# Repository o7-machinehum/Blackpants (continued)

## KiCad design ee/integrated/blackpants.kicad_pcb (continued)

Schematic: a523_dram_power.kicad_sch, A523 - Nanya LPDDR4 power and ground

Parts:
C310: 10uF; C_0603_1608Metric; Voltage 10V
C311, C312, C313, C314, C315, C316, C317: 2.2uF; C_0402_1005Metric; Voltage 10V
C318: 100nF; C_0402_1005Metric; Voltage 10V
U301: NT6AN512T32AV-J2; FBGA-200_10x15mm_P0.8x0.65mm

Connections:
GND: C310.2, C311.2, C312.2, C313.2, C314.2, C315.2, C316.2, C317.2, C318.2, U301.A3 (VSS), U301.A10 (VSS), U301.AB3 (VSS), U301.AB5 (VSS), U301.AB8 (VSS), U301.AB10 (VSS), U301.C1 (VSS), U301.C5 (VSS), U301.C8 (VSS), U301.C12 (VSS), U301.D2 (VSS), U301.D4 (VSS), U301.D9 (VSS), U301.D11 (VSS), U301.E1 (VSS), U301.E5 (VSS), U301.E8 (VSS), U301.E12 (VSS), U301.G1 (VSS), U301.G3 (VSS), U301.G5 (VSS), U301.G8 (VSS), U301.G10 (VSS), U301.G12 (VSS), U301.J1 (VSS), U301.J3 (VSS), U301.J10 (VSS), U301.J12 (VSS), U301.K2 (VSS), U301.K4 (VSS), U301.K9 (VSS), U301.K11 (VSS), U301.N2 (VSS), U301.N4 (VSS), U301.N9 (VSS), U301.N11 (VSS), U301.P1 (VSS), U301.P3 (VSS), U301.P10 (VSS), U301.P12 (VSS), U301.T1 (VSS), U301.T3 (VSS), U301.T5 (VSS), U301.T8 (VSS), U301.T10 (VSS), U301.T12 (VSS), U301.V1 (VSS), U301.V5 (VSS), U301.V8 (VSS), U301.V12 (VSS), U301.W2 (VSS), U301.W4 (VSS), U301.W9 (VSS), U301.W11 (VSS), U301.Y1 (VSS), U301.Y5 (VSS), U301.Y8 (VSS), U301.Y12 (VSS); also elsewhere on the board
VCC_DRAM: C310.1, C311.1, C312.1, C313.1, C314.1, C315.1, C316.1, U301.A4 (VDD2), U301.A9 (VDD2), U301.AA3 (VDDQ), U301.AA5 (VDDQ), U301.AA8 (VDDQ), U301.AA10 (VDDQ), U301.AB4 (VDD2), U301.AB9 (VDD2), U301.B3 (VDDQ), U301.B5 (VDDQ), U301.B8 (VDDQ), U301.B10 (VDDQ), U301.D1 (VDDQ), U301.D5 (VDDQ), U301.D8 (VDDQ), U301.D12 (VDDQ), U301.F3 (VDDQ), U301.F5 (VDD2), U301.F8 (VDD2), U301.F10 (VDDQ), U301.H1 (VDD2), U301.H5 (VDD2), U301.H8 (VDD2), U301.H12 (VDD2), U301.K1 (VDD2), U301.K3 (VDD2), U301.K10 (VDD2), U301.K12 (VDD2), U301.N1 (VDD2), U301.N3 (VDD2), U301.N10 (VDD2), U301.N12 (VDD2), U301.R1 (VDD2), U301.R5 (VDD2), U301.R8 (VDD2), U301.R12 (VDD2), U301.U3 (VDDQ), U301.U5 (VDD2), U301.U8 (VDD2), U301.U10 (VDDQ), U301.W1 (VDDQ), U301.W5 (VDDQ), U301.W8 (VDDQ), U301.W12 (VDDQ); also elsewhere on the board
VDD18_LPDDR: C317.1, C318.1, U301.F1 (VDD1), U301.F12 (VDD1), U301.G4 (VDD1), U301.G9 (VDD1), U301.T4 (VDD1), U301.T9 (VDD1), U301.U1 (VDD1), U301.U12 (VDD1); also elsewhere on the board

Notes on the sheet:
VDD1 = 1.8V BLDO2. VDD2 = VDDQ = 1.1V DCDC3. DNU pads: no tracks or vias. Place the capacitors beside the DRAM package. Follow Allwinner DDR constraints and the selected stack-up.

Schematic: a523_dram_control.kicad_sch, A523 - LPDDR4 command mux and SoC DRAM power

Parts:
C301, C302, C303, C304, C305, C306, C307, C308: 2.2uF; C_0402_1005Metric; Voltage 10V
C309: 100nF; C_0402_1005Metric; Voltage 10V
NT301: DRAM sense; NetTie-2_SMD_Pad0.5mm
R301: 120 / 1%; R_0402_1005Metric
R302: 240 / 1%; R_0402_1005Metric
U201: A523; Allwinner_A523_FCCSP-522_15x15mm_P0.5mm
U301: NT6AN512T32AV-J2; FBGA-200_10x15mm_P0.8x0.65mm

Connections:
/2GB LPDDR4/Command / DRAM supply/DDR_CA0_0: U201.AE29 (SA2), U301.H2 (CA0_a)
/2GB LPDDR4/Command / DRAM supply/DDR_CA0_1: U201.AE28 (SA11), U301.J2 (CA1_a)
/2GB LPDDR4/Command / DRAM supply/DDR_CA0_2: U201.AC26 (SA1), U301.H9 (CA2_a)
/2GB LPDDR4/Command / DRAM supply/DDR_CA0_3: U201.AC25 (SA10), U301.H10 (CA3_a)
/2GB LPDDR4/Command / DRAM supply/DDR_CA0_4: U201.AE26 (SA17), U301.H11 (CA4_a)
/2GB LPDDR4/Command / DRAM supply/DDR_CA0_5: U201.AE27 (SA9), U301.J11 (CA5_a)
/2GB LPDDR4/Command / DRAM supply/DDR_CA1_0: U201.AE21 (SBA1), U301.R2 (CA0_b)
/2GB LPDDR4/Command / DRAM supply/DDR_CA1_1: U201.AD21 (SA4), U301.P2 (CA1_b)
/2GB LPDDR4/Command / DRAM supply/DDR_CA1_2: U201.AG21 (SA8), U301.R9 (CA2_b)
/2GB LPDDR4/Command / DRAM supply/DDR_CA1_3: U201.AF21 (SBA0), U301.R10 (CA3_b)
/2GB LPDDR4/Command / DRAM supply/DDR_CA1_4: U201.AE23 (SA16), U301.R11 (CA4_b)
/2GB LPDDR4/Command / DRAM supply/DDR_CA1_5: U201.AG25 (SACT), U301.P11 (CA5_b)
/2GB LPDDR4/Command / DRAM supply/DDR_CK0_N: U201.AJ26 (SCKN), U301.J9 (CK_N_a)
/2GB LPDDR4/Command / DRAM supply/DDR_CK0_P: U201.AH26 (SCKP), U301.J8 (CK_P_a)
/2GB LPDDR4/Command / DRAM supply/DDR_CK1_N: U201.AJ25 (SA15), U301.P9 (CK_N_b)
/2GB LPDDR4/Command / DRAM supply/DDR_CK1_P: U201.AH24 (SA14), U301.P8 (CK_P_b)
/2GB LPDDR4/Command / DRAM supply/DDR_CKE0: U201.AH27 (SCKE0), U301.J4 (CKE_a)
/2GB LPDDR4/Command / DRAM supply/DDR_CKE1: U201.AJ23 (SA6), U301.P4 (CKE_b)
/2GB LPDDR4/Command / DRAM supply/DDR_CS0: U201.AJ28 (SCS0), U301.H4 (CS_a)
/2GB LPDDR4/Command / DRAM supply/DDR_CS1: U201.AF25 (SA13), U301.R4 (CS_b)
/2GB LPDDR4/Command / DRAM supply/DDR_RESET_N: U201.AC19 (SRST), U301.T11 (RESET_N)
/2GB LPDDR4/Command / DRAM supply/DDR_ZQ: R302.2, U301.A5 (ZQ)
/2GB LPDDR4/Command / DRAM supply/SOC_DDR_ZQ: R301.1, U201.U25 (SZQ)
/VCC_DRAM_FB: NT301.2; also elsewhere on the board
GND: C301.2, C302.2, C303.2, C304.2, C305.2, C306.2, C307.2, C308.2, C309.2, R301.2; also elsewhere on the board
VCC_AVCC: C309.1, U201.AA21 (VDD18-DRAM); also elsewhere on the board
VCC_DRAM: C301.1, C302.1, C303.1, C304.1, C305.1, C306.1, C307.1, C308.1, NT301.1, R302.1, U201.T20 (VCC-DRAM), U201.T21 (VCC-DRAM), U201.T22 (VCC-DRAM), U201.U21 (VCC-DRAM), U201.V21 (VCC-DRAM), U201.W21 (VCC-DRAM), U201.Y14 (VCC-DRAML), U201.Y15 (VCC-DRAML), U201.Y16 (VCC-DRAML), U201.Y17 (VCC-DRAML), U201.Y19 (VCC-DRAML), U201.Y21 (VCC-DRAM), U301.G2 (ODT_CA_a), U301.T2 (ODT_CA_b); also elsewhere on the board

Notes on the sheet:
A523 LPDDR4 command mapping / load-side feedback
NT301: load-side sense to U501 FB3; allow >= 30mA. VCC_DRAM and VCC_DRAML both use 1.1V for LPDDR4. C301..C308 belong at the SoC DRAM ball clusters. Unused DDR3 command functions are unconnected.

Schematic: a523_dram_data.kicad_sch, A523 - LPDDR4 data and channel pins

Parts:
U201: A523; Allwinner_A523_FCCSP-522_15x15mm_P0.5mm
U301: NT6AN512T32AV-J2; FBGA-200_10x15mm_P0.8x0.65mm

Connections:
/2GB LPDDR4/Data channels/DDR_DM0: U201.AA29 (SDQM0), U301.C3 (DMI0_a)
/2GB LPDDR4/Data channels/DDR_DM1: U201.W28 (SDQM1), U301.C10 (DMI1_a)
/2GB LPDDR4/Data channels/DDR_DM2: U201.AH20 (SDQM2), U301.Y3 (DMI0_b)
/2GB LPDDR4/Data channels/DDR_DM3: U201.AJ16 (SDQM3), U301.Y10 (DMI1_b)
/2GB LPDDR4/Data channels/DDR_DQ0: U201.AA24 (SDQ0), U301.E4 (DQ5_a)
/2GB LPDDR4/Data channels/DDR_DQ1: U201.AA23 (SDQ1), U301.F4 (DQ4_a)
/2GB LPDDR4/Data channels/DDR_DQ2: U201.AC28 (SDQ2), U301.E2 (DQ2_a)
/2GB LPDDR4/Data channels/DDR_DQ3: U201.AD29 (SDQ3), U301.F2 (DQ3_a)
/2GB LPDDR4/Data channels/DDR_DQ4: U201.AA26 (SDQ4), U301.B2 (DQ0_a)
/2GB LPDDR4/Data channels/DDR_DQ5: U201.Y28 (SDQ5), U301.B4 (DQ7_a)
/2GB LPDDR4/Data channels/DDR_DQ6: U201.AA27 (SDQ6), U301.C2 (DQ1_a)
/2GB LPDDR4/Data channels/DDR_DQ7: U201.Y29 (SDQ7), U301.C4 (DQ6_a)
/2GB LPDDR4/Data channels/DDR_DQ8: U201.W23 (SDQ8), U301.E9 (DQ13_a)
/2GB LPDDR4/Data channels/DDR_DQ9: U201.W24 (SDQ9), U301.F9 (DQ12_a)
/2GB LPDDR4/Data channels/DDR_DQ10: U201.W26 (SDQ10), U301.B9 (DQ15_a)
/2GB LPDDR4/Data channels/DDR_DQ11: U201.W27 (SDQ11), U301.C9 (DQ14_a)
/2GB LPDDR4/Data channels/DDR_DQ12: U201.U29 (SDQ12), U301.C11 (DQ9_a)
/2GB LPDDR4/Data channels/DDR_DQ13: U201.U27 (SDQ13), U301.B11 (DQ8_a)
/2GB LPDDR4/Data channels/DDR_DQ14: U201.U24 (SDQ14), U301.F11 (DQ11_a)
/2GB LPDDR4/Data channels/DDR_DQ15: U201.U23 (SDQ15), U301.E11 (DQ10_a)
/2GB LPDDR4/Data channels/DDR_DQ16: U201.AH21 (SDQ16), U301.U2 (DQ3_b)
/2GB LPDDR4/Data channels/DDR_DQ17: U201.AJ21 (SDQ17), U301.V2 (DQ2_b)
/2GB LPDDR4/Data channels/DDR_DQ18: U201.AD19 (SDQ18), U301.U4 (DQ4_b)
/2GB LPDDR4/Data channels/DDR_DQ19: U201.AF19 (SDQ19), U301.Y2 (DQ1_b)
/2GB LPDDR4/Data channels/DDR_DQ20: U201.AG19 (SDQ20), U301.V4 (DQ5_b)
/2GB LPDDR4/Data channels/DDR_DQ21: U201.AH18 (SDQ21), U301.AA2 (DQ0_b)
/2GB LPDDR4/Data channels/DDR_DQ22: U201.AJ17 (SDQ22), U301.AA4 (DQ7_b)
/2GB LPDDR4/Data channels/DDR_DQ23: U201.AC17 (SDQ23), U301.Y4 (DQ6_b)
/2GB LPDDR4/Data channels/DDR_DQ24: U201.AC15 (SDQ24), U301.AA9 (DQ15_b)
/2GB LPDDR4/Data channels/DDR_DQ25: U201.AD15 (SDQ25), U301.AA11 (DQ8_b)
/2GB LPDDR4/Data channels/DDR_DQ26: U201.AF15 (SDQ26), U301.V11 (DQ10_b)
/2GB LPDDR4/Data channels/DDR_DQ27: U201.AG15 (SDQ27), U301.Y11 (DQ9_b)
/2GB LPDDR4/Data channels/DDR_DQ28: U201.AH17 (SDQ28), U301.U9 (DQ12_b)
/2GB LPDDR4/Data channels/DDR_DQ29: U201.AG17 (SDQ29), U301.U11 (DQ11_b)
/2GB LPDDR4/Data channels/DDR_DQ30: U201.AF17 (SDQ30), U301.Y9 (DQ14_b)
/2GB LPDDR4/Data channels/DDR_DQ31: U201.AD17 (SDQ31), U301.V9 (DQ13_b)
/2GB LPDDR4/Data channels/DDR_DQS0N: U201.AB29 (SDQS0N), U301.E3 (DQS_N0_a)
/2GB LPDDR4/Data channels/DDR_DQS0P: U201.AB28 (SDQS0P), U301.D3 (DQS_P0_a)
/2GB LPDDR4/Data channels/DDR_DQS1N: U201.V29 (SDQS1N), U301.E10 (DQS_N1_a)
/2GB LPDDR4/Data channels/DDR_DQS1P: U201.V28 (SDQS1P), U301.D10 (DQS_P1_a)
/2GB LPDDR4/Data channels/DDR_DQS2N: U201.AJ19 (SDQS2N), U301.V3 (DQS_N0_b)
/2GB LPDDR4/Data channels/DDR_DQS2P: U201.AH19 (SDQS2P), U301.W3 (DQS_P0_b)
/2GB LPDDR4/Data channels/DDR_DQS3N: U201.AJ15 (SDQS3N), U301.V10 (DQS_N1_b)
/2GB LPDDR4/Data channels/DDR_DQS3P: U201.AH15 (SDQS3P), U301.W10 (DQS_P1_b)

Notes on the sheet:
Vendor-qualified clock target: 1200MHz. Use NT6AN512T32AV-J2 parameters in the DRAM firmware. Final clock and timings require board validation.
Channel A: DQ[0..15], DQS/DM[0..1] Channel B: DQ[16..31], DQS/DM[2..3] One rank per channel. Command and power on following pages.
2 GB LPDDR4 / 2 x 16-bit channels / single rank per channel
DQ bit swaps follow Allwinner S6L V2.0 (C0402). DDR_DQ labels identify SoC bits; RAM pin names show the swizzle. Swaps stay within each byte. DQS and DMI assignments are unchanged.

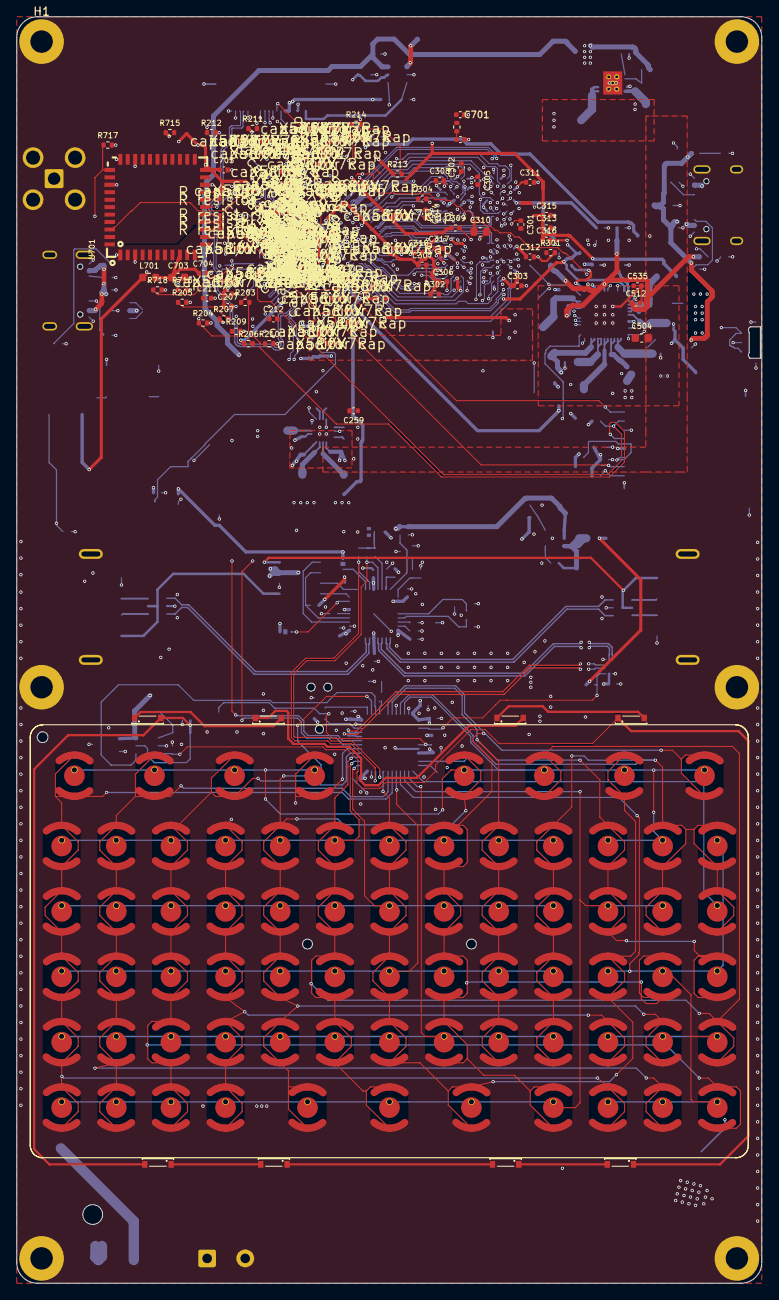
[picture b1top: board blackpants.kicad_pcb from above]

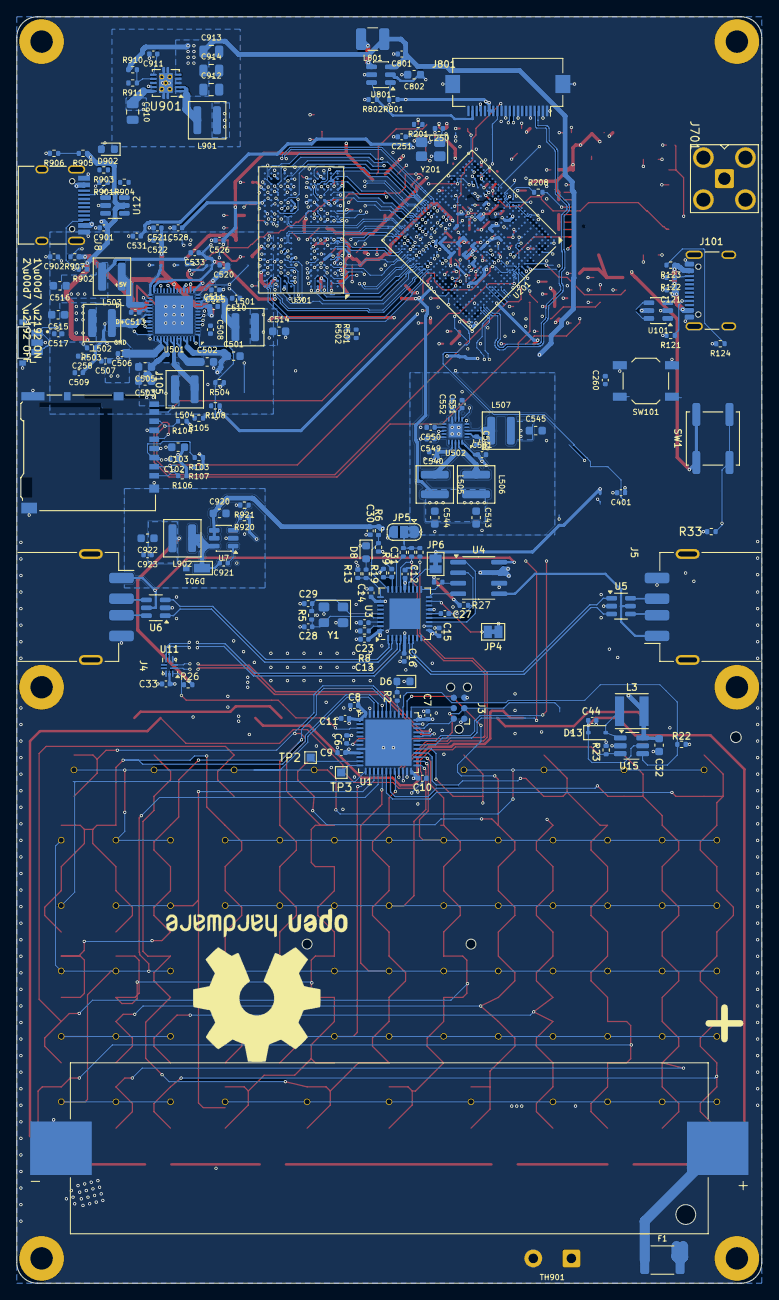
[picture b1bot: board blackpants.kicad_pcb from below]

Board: 6 copper layers, 90.0 x 153.0 mm, 300 parts (174 on the bottom side), 265 nets.

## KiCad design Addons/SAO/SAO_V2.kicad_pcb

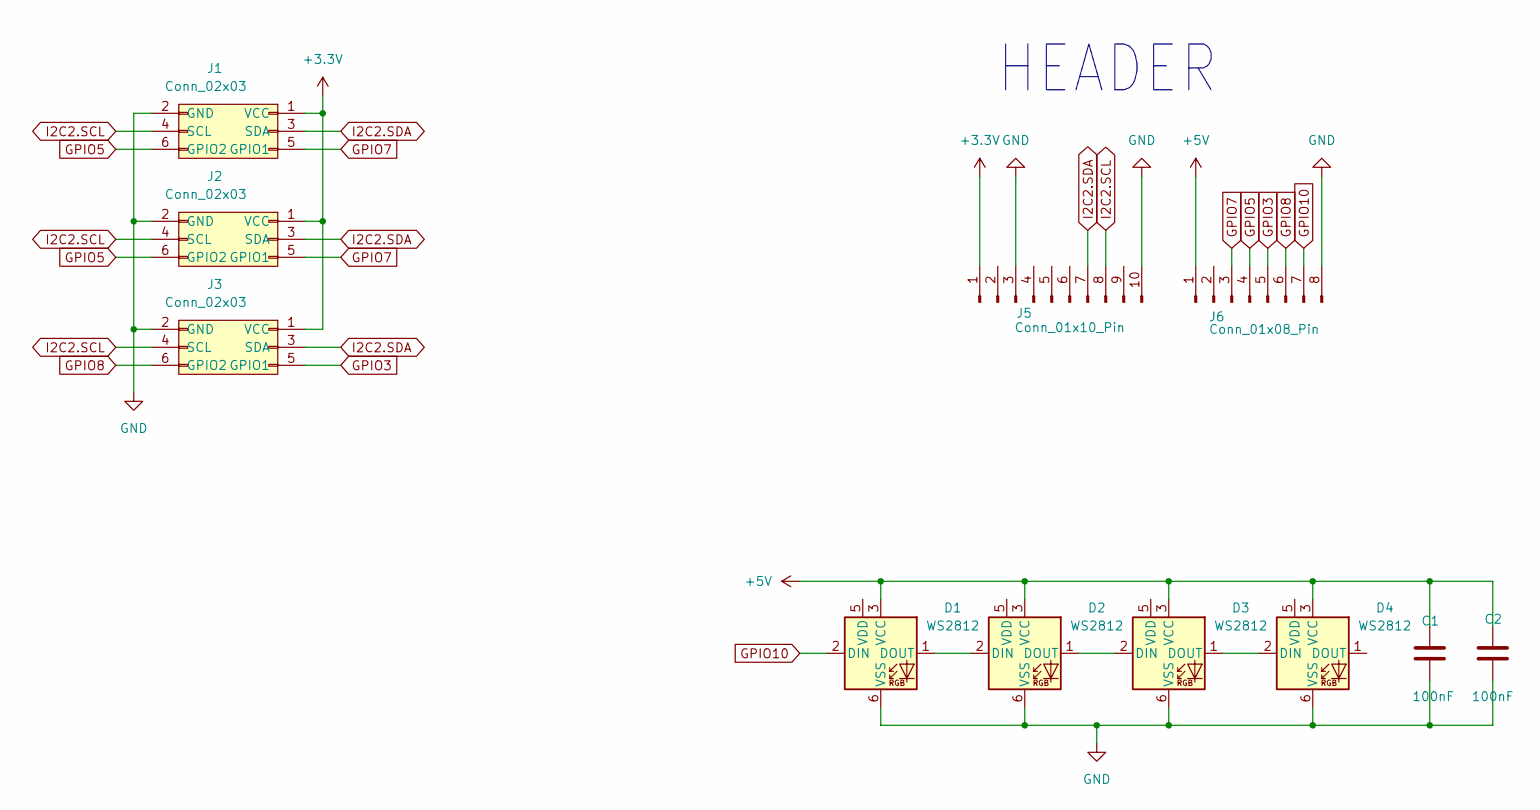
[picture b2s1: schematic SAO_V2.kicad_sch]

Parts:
C1, C2: 100nF; C_0805_2012Metric
D1, D2, D3, D4: WS2812; LED_WS2812_PLCC6_5.0x5.0mm_P1.6mm
J1, J2, J3: Conn_02x03; PinHeader_2x03_P2.54mm_Vertical; LCSC C492420
J5: Conn_01x10_Pin; PinHeader_1x10_P2.54mm_Horizontal
J6: Conn_01x08_Pin; PinHeader_1x08_P2.54mm_Horizontal

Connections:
+3.3V: J1.1 (VCC), J2.1 (VCC), J3.1 (VCC), J5.1
+5V: C1.1, C2.1, D1.3 (VCC), D2.3 (VCC), D3.3 (VCC), D4.3 (VCC), J6.1
GND: C1.2, C2.2, D1.6 (VSS), D2.6 (VSS), D3.6 (VSS), D4.6 (VSS), J1.2 (GND), J2.2 (GND), J3.2 (GND), J5.3, J5.10, J6.8
GPIO3: J3.5 (GPIO1), J6.5
GPIO5: J1.6 (GPIO2), J2.6 (GPIO2), J6.4
GPIO7: J1.5 (GPIO1), J2.5 (GPIO1), J6.3
GPIO8: J3.6 (GPIO2), J6.6
GPIO10: D1.2 (DIN), J6.7
I2C2.SCL: J1.4 (SCL), J2.4 (SCL), J3.4 (SCL), J5.8
I2C2.SDA: J1.3 (SDA), J2.3 (SDA), J3.3 (SDA), J5.7
unnamed: D1.1 (DOUT), D2.2 (DIN)
unnamed: D2.1 (DOUT), D3.2 (DIN)
unnamed: D3.1 (DOUT), D4.2 (DIN)

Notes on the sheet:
HEADER

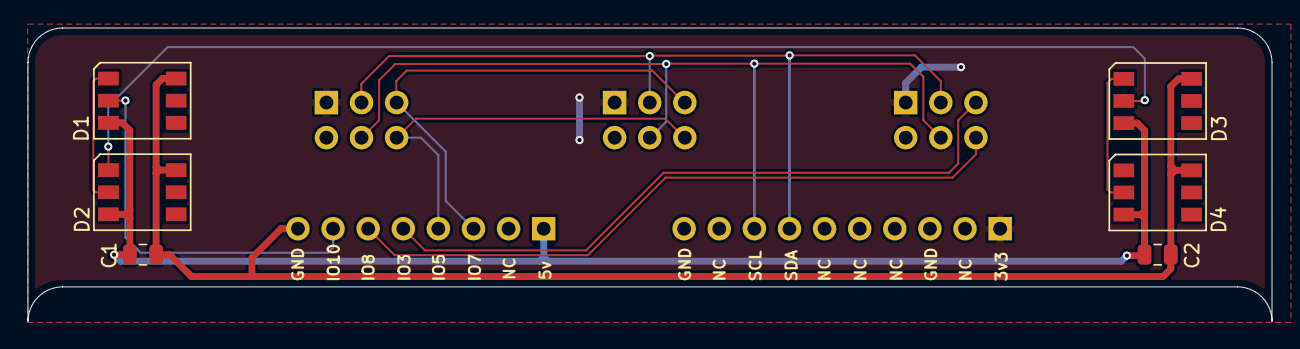
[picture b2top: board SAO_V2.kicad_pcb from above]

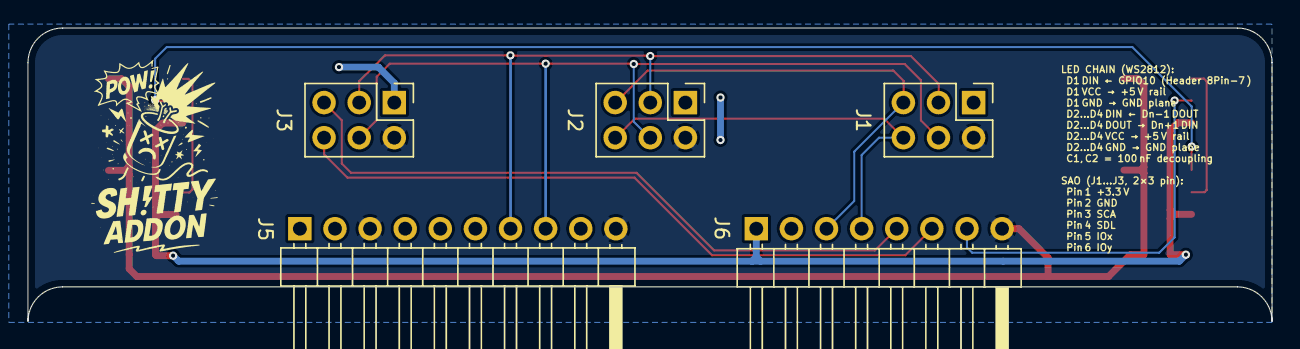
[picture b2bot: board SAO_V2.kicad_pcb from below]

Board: 2 copper layers, 90.0 x 21.2 mm, 11 parts (3 on the bottom side), 13 nets.

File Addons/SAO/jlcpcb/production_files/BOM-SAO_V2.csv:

Comment,Designator,Footprint,LCSC,Quantity
WS2812,"D1,D2,D3,D4",LED_WS2812_PLCC6_5.0x5.0mm_P1.6mm,C2761795,4
Conn_02x03,"J1,J2,J3",PinHeader_2x03_P2.54mm_Vertical,C492420,3
100nF,"C1,C2",C_0805_2012Metric,C49678,2
Conn_01x10_Pin,J5,PinHeader_1x10_P2.54mm_Horizontal,,1
Conn_01x08_Pin,J6,PinHeader_1x08_P2.54mm_Horizontal,,1

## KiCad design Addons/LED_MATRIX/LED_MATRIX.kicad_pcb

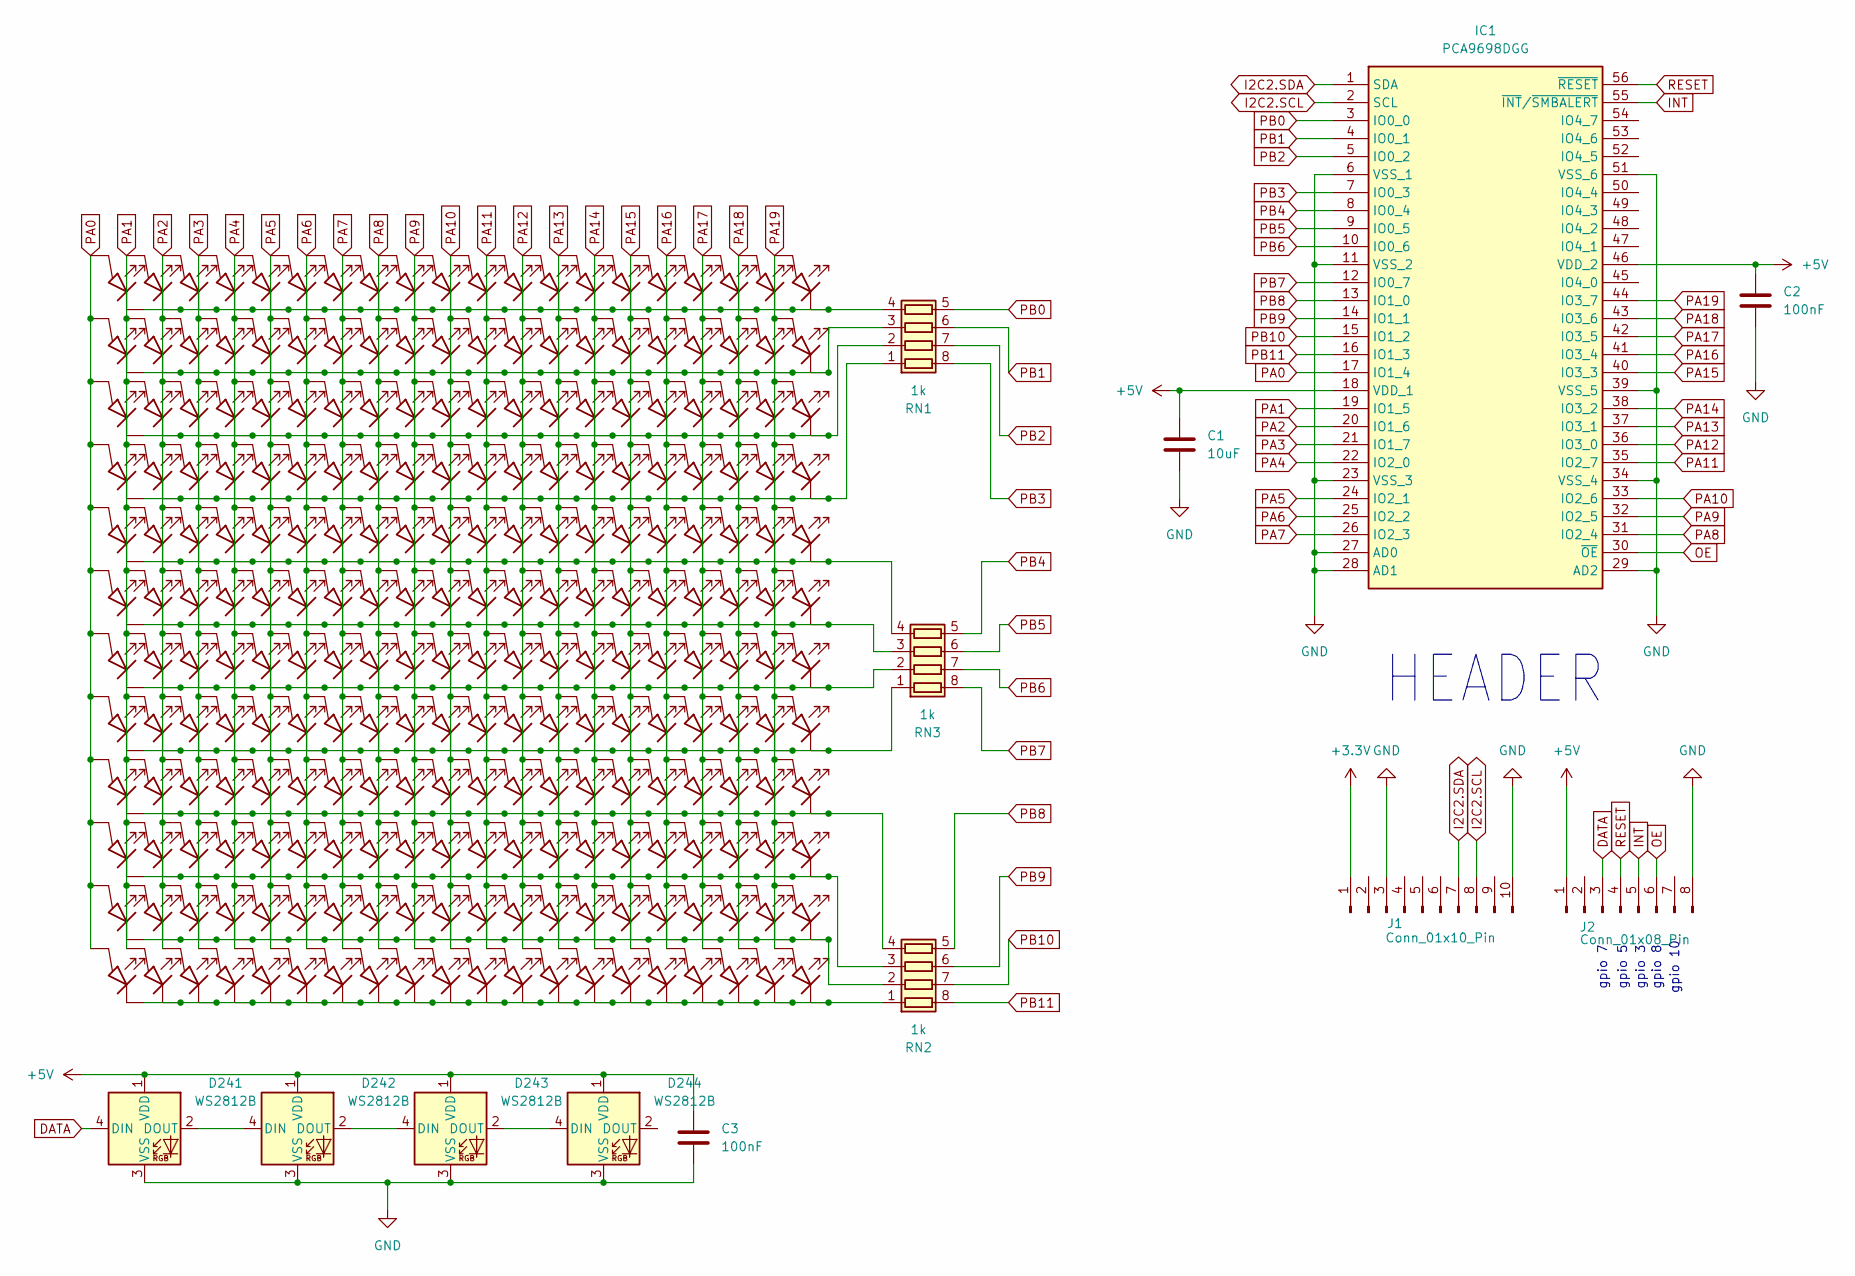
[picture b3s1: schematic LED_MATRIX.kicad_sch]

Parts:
C1: 10uF; C_0805_2012Metric; LCSC Part Number C1713
C2, C3: 100nF; C_0805_2012Metric; LCSC Part Number C1711
D1, D2, D3, D4, D5, D6, D7, D8, D9, D10, D11, D12, D13, D14, D15, D16, D17, D18, D19, D20, D21, D22, D23, D24, D25, D26, D27, D28, D29, D30, D31, D32, D33, D34, D35, D36, D37, D38, D39, D40, D41, D42, D43, D44, D45, D46, D47, D48, D49, D50, D51, D52, D53, D54, D55, D56, D57, D58, D59, D60, D61, D62, D63, D64, D65, D66, D67, D68, D69, D70, D71, D72, D73, D74, D75, D76, D77, D78, D79, D80, D81, D82, D83, D84, D85, D86, D87, D88, D89, D90, D91, D92, D93, D94, D95, D96, D97, D98, D99, D100, D101, D102, D103, D104, D105, D106, D107, D108, D109, D110, D111, D112, D113, D114, D115, D116, D117, D118, D119, D120, D121, D122, D123, D124, D125, D126, D127, D128, D129, D130, D131, D132, D133, D134, D135, D136, D137, D138, D139, D140, D141, D142, D143, D144, D145, D146, D147, D148, D149, D150, D151, D152, D153, D154, D155, D156, D157, D158, D159, D160, D161, D162, D163, D164, D165, D166, D167, D168, D169, D170, D171, D172, D173, D174, D175, D176, D177, D178, D179, D180, D181, D182, D183, D184, D185, D186, D187, D188, D189, D190, D191, D192, D193, D194, D195, D196, D197, D198, D199, D200, D201, D202, D203, D204, D205, D206, D207, D208, D209, D210, D211, D212, D213, D214, D215, D216, D217, D218, D219, D220, D221, D222, D223, D224, D225, D226, D227, D228, D229, D230, D231, D232, D233, D234, D235, D236, D237, D238, D239, D240: LED0603; LED_0603_1608Metric; LCSC C205448
D241, D242, D243, D244: WS2812B; LED_WS2812B_PLCC4_5.0x5.0mm_P3.2mm; LCSC Part Number C2843785
IC1: PCA9698DGG; SOP50P810X120-56N; Manufacturer_Part_Number PCA9698DGG; LCSC Part Number C729177
J1: Conn_01x10_Pin; PinHeader_1x10_P2.54mm_Horizontal
J2: Conn_01x08_Pin; PinHeader_1x08_P2.54mm_Horizontal
RN1, RN2, RN3: 1k; R_Array_Concave_4x0603; LCSC Part Number C111803

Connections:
+3.3V: J1.1
+5V: C1.1, C2.1, C3.1, D241.1 (VDD), D242.1 (VDD), D243.1 (VDD), D244.1 (VDD), IC1.18 (VDD_1), IC1.46 (VDD_2), J2.1
DATA: D241.4 (DIN), J2.3
GND: C1.2, C2.2, C3.2, D241.3 (VSS), D242.3 (VSS), D243.3 (VSS), D244.3 (VSS), IC1.6 (VSS_1), IC1.11 (VSS_2), IC1.23 (VSS_3), IC1.27 (AD0), IC1.28 (AD1), IC1.29 (AD2), IC1.34 (VSS_4), IC1.39 (VSS_5), IC1.51 (VSS_6), J1.3, J1.10, J2.8
I2C2.SCL: IC1.2 (SCL), J1.8
I2C2.SDA: IC1.1 (SDA), J1.7
INT: IC1.55 (~INT/~SMBALERT), J2.5
unnamed: D1.1 (K), D13.1 (K), D25.1 (K), D37.1 (K), D49.1 (K), D61.1 (K), D73.1 (K), D85.1 (K), D97.1 (K), D109.1 (K), D121.1 (K), D133.1 (K), D145.1 (K), D157.1 (K), D169.1 (K), D181.1 (K), D193.1 (K), D205.1 (K), D217.1 (K), D229.1 (K), RN1.4 (R4.1)
unnamed: D10.1 (K), D22.1 (K), D34.1 (K), D46.1 (K), D58.1 (K), D70.1 (K), D82.1 (K), D94.1 (K), D106.1 (K), D118.1 (K), D130.1 (K), D142.1 (K), D154.1 (K), D166.1 (K), D178.1 (K), D190.1 (K), D202.1 (K), D214.1 (K), D226.1 (K), D238.1 (K), RN2.3 (R3.1)
unnamed: D4.1 (K), D16.1 (K), D28.1 (K), D40.1 (K), D52.1 (K), D64.1 (K), D76.1 (K), D88.1 (K), D100.1 (K), D112.1 (K), D124.1 (K), D136.1 (K), D148.1 (K), D160.1 (K), D172.1 (K), D184.1 (K), D196.1 (K), D208.1 (K), D220.1 (K), D232.1 (K), RN1.1 (R1.1)
unnamed: D5.1 (K), D17.1 (K), D29.1 (K), D41.1 (K), D53.1 (K), D65.1 (K), D77.1 (K), D89.1 (K), D101.1 (K), D113.1 (K), D125.1 (K), D137.1 (K), D149.1 (K), D161.1 (K), D173.1 (K), D185.1 (K), D197.1 (K), D209.1 (K), D221.1 (K), D233.1 (K), RN3.4 (R4.1)
unnamed: D6.1 (K), D18.1 (K), D30.1 (K), D42.1 (K), D54.1 (K), D66.1 (K), D78.1 (K), D90.1 (K), D102.1 (K), D114.1 (K), D126.1 (K), D138.1 (K), D150.1 (K), D162.1 (K), D174.1 (K), D186.1 (K), D198.1 (K), D210.1 (K), D222.1 (K), D234.1 (K), RN3.3 (R3.1)
unnamed: D7.1 (K), D19.1 (K), D31.1 (K), D43.1 (K), D55.1 (K), D67.1 (K), D79.1 (K), D91.1 (K), D103.1 (K), D115.1 (K), D127.1 (K), D139.1 (K), D151.1 (K), D163.1 (K), D175.1 (K), D187.1 (K), D199.1 (K), D211.1 (K), D223.1 (K), D235.1 (K), RN3.2 (R2.1)
unnamed: D8.1 (K), D20.1 (K), D32.1 (K), D44.1 (K), D56.1 (K), D68.1 (K), D80.1 (K), D92.1 (K), D104.1 (K), D116.1 (K), D128.1 (K), D140.1 (K), D152.1 (K), D164.1 (K), D176.1 (K), D188.1 (K), D200.1 (K), D212.1 (K), D224.1 (K), D236.1 (K), RN3.1 (R1.1)
unnamed: D9.1 (K), D21.1 (K), D33.1 (K), D45.1 (K), D57.1 (K), D69.1 (K), D81.1 (K), D93.1 (K), D105.1 (K), D117.1 (K), D129.1 (K), D141.1 (K), D153.1 (K), D165.1 (K), D177.1 (K), D189.1 (K), D201.1 (K), D213.1 (K), D225.1 (K), D237.1 (K), RN2.4 (R4.1)
unnamed: D11.1 (K), D23.1 (K), D35.1 (K), D47.1 (K), D59.1 (K), D71.1 (K), D83.1 (K), D95.1 (K), D107.1 (K), D119.1 (K), D131.1 (K), D143.1 (K), D155.1 (K), D167.1 (K), D179.1 (K), D191.1 (K), D203.1 (K), D215.1 (K), D227.1 (K), D239.1 (K), RN2.2 (R2.1)
unnamed: D12.1 (K), D24.1 (K), D36.1 (K), D48.1 (K), D60.1 (K), D72.1 (K), D84.1 (K), D96.1 (K), D108.1 (K), D120.1 (K), D132.1 (K), D144.1 (K), D156.1 (K), D168.1 (K), D180.1 (K), D192.1 (K), D204.1 (K), D216.1 (K), D228.1 (K), D240.1 (K), RN2.1 (R1.1)
unnamed: D2.1 (K), D14.1 (K), D26.1 (K), D38.1 (K), D50.1 (K), D62.1 (K), D74.1 (K), D86.1 (K), D98.1 (K), D110.1 (K), D122.1 (K), D134.1 (K), D146.1 (K), D158.1 (K), D170.1 (K), D182.1 (K), D194.1 (K), D206.1 (K), D218.1 (K), D230.1 (K), RN1.3 (R3.1)
unnamed: D3.1 (K), D15.1 (K), D27.1 (K), D39.1 (K), D51.1 (K), D63.1 (K), D75.1 (K), D87.1 (K), D99.1 (K), D111.1 (K), D123.1 (K), D135.1 (K), D147.1 (K), D159.1 (K), D171.1 (K), D183.1 (K), D195.1 (K), D207.1 (K), D219.1 (K), D231.1 (K), RN1.2 (R2.1)
unnamed: D241.2 (DOUT), D242.4 (DIN)
unnamed: D242.2 (DOUT), D243.4 (DIN)
unnamed: D243.2 (DOUT), D244.4 (DIN)
OE: IC1.30 (~OE), J2.6
PA0: D1.2 (A), D2.2 (A), D3.2 (A), D4.2 (A), D5.2 (A), D6.2 (A), D7.2 (A), D8.2 (A), D9.2 (A), D10.2 (A), D11.2 (A), D12.2 (A), IC1.17 (IO1_4)
PA1: D13.2 (A), D14.2 (A), D15.2 (A), D16.2 (A), D17.2 (A), D18.2 (A), D19.2 (A), D20.2 (A), D21.2 (A), D22.2 (A), D23.2 (A), D24.2 (A), IC1.19 (IO1_5)
PA2: D25.2 (A), D26.2 (A), D27.2 (A), D28.2 (A), D29.2 (A), D30.2 (A), D31.2 (A), D32.2 (A), D33.2 (A), D34.2 (A), D35.2 (A), D36.2 (A), IC1.20 (IO1_6)
PA3: D37.2 (A), D38.2 (A), D39.2 (A), D40.2 (A), D41.2 (A), D42.2 (A), D43.2 (A), D44.2 (A), D45.2 (A), D46.2 (A), D47.2 (A), D48.2 (A), IC1.21 (IO1_7)
PA4: D49.2 (A), D50.2 (A), D51.2 (A), D52.2 (A), D53.2 (A), D54.2 (A), D55.2 (A), D56.2 (A), D57.2 (A), D58.2 (A), D59.2 (A), D60.2 (A), IC1.22 (IO2_0)
PA5: D61.2 (A), D62.2 (A), D63.2 (A), D64.2 (A), D65.2 (A), D66.2 (A), D67.2 (A), D68.2 (A), D69.2 (A), D70.2 (A), D71.2 (A), D72.2 (A), IC1.24 (IO2_1)
PA6: D73.2 (A), D74.2 (A), D75.2 (A), D76.2 (A), D77.2 (A), D78.2 (A), D79.2 (A), D80.2 (A), D81.2 (A), D82.2 (A), D83.2 (A), D84.2 (A), IC1.25 (IO2_2)
PA7: D85.2 (A), D86.2 (A), D87.2 (A), D88.2 (A), D89.2 (A), D90.2 (A), D91.2 (A), D92.2 (A), D93.2 (A), D94.2 (A), D95.2 (A), D96.2 (A), IC1.26 (IO2_3)
PA8: D97.2 (A), D98.2 (A), D99.2 (A), D100.2 (A), D101.2 (A), D102.2 (A), D103.2 (A), D104.2 (A), D105.2 (A), D106.2 (A), D107.2 (A), D108.2 (A), IC1.31 (IO2_4)
PA9: D109.2 (A), D110.2 (A), D111.2 (A), D112.2 (A), D113.2 (A), D114.2 (A), D115.2 (A), D116.2 (A), D117.2 (A), D118.2 (A), D119.2 (A), D120.2 (A), IC1.32 (IO2_5)
PA10: D121.2 (A), D122.2 (A), D123.2 (A), D124.2 (A), D125.2 (A), D126.2 (A), D127.2 (A), D128.2 (A), D129.2 (A), D130.2 (A), D131.2 (A), D132.2 (A), IC1.33 (IO2_6)
PA11: D133.2 (A), D134.2 (A), D135.2 (A), D136.2 (A), D137.2 (A), D138.2 (A), D139.2 (A), D140.2 (A), D141.2 (A), D142.2 (A), D143.2 (A), D144.2 (A), IC1.35 (IO2_7)
PA12: D145.2 (A), D146.2 (A), D147.2 (A), D148.2 (A), D149.2 (A), D150.2 (A), D151.2 (A), D152.2 (A), D153.2 (A), D154.2 (A), D155.2 (A), D156.2 (A), IC1.36 (IO3_0)
PA13: D157.2 (A), D158.2 (A), D159.2 (A), D160.2 (A), D161.2 (A), D162.2 (A), D163.2 (A), D164.2 (A), D165.2 (A), D166.2 (A), D167.2 (A), D168.2 (A), IC1.37 (IO3_1)
PA14: D169.2 (A), D170.2 (A), D171.2 (A), D172.2 (A), D173.2 (A), D174.2 (A), D175.2 (A), D176.2 (A), D177.2 (A), D178.2 (A), D179.2 (A), D180.2 (A), IC1.38 (IO3_2)
PA15: D181.2 (A), D182.2 (A), D183.2 (A), D184.2 (A), D185.2 (A), D186.2 (A), D187.2 (A), D188.2 (A), D189.2 (A), D190.2 (A), D191.2 (A), D192.2 (A), IC1.40 (IO3_3)
PA16: D193.2 (A), D194.2 (A), D195.2 (A), D196.2 (A), D197.2 (A), D198.2 (A), D199.2 (A), D200.2 (A), D201.2 (A), D202.2 (A), D203.2 (A), D204.2 (A), IC1.41 (IO3_4)
PA17: D205.2 (A), D206.2 (A), D207.2 (A), D208.2 (A), D209.2 (A), D210.2 (A), D211.2 (A), D212.2 (A), D213.2 (A), D214.2 (A), D215.2 (A), D216.2 (A), IC1.42 (IO3_5)
PA18: D217.2 (A), D218.2 (A), D219.2 (A), D220.2 (A), D221.2 (A), D222.2 (A), D223.2 (A), D224.2 (A), D225.2 (A), D226.2 (A), D227.2 (A), D228.2 (A), IC1.43 (IO3_6)
PA19: D229.2 (A), D230.2 (A), D231.2 (A), D232.2 (A), D233.2 (A), D234.2 (A), D235.2 (A), D236.2 (A), D237.2 (A), D238.2 (A), D239.2 (A), D240.2 (A), IC1.44 (IO3_7)
PB0: IC1.3 (IO0_0), RN1.5 (R4.2)
PB1: IC1.4 (IO0_1), RN1.6 (R3.2)
PB2: IC1.5 (IO0_2), RN1.7 (R2.2)
PB3: IC1.7 (IO0_3), RN1.8 (R1.2)
PB4: IC1.8 (IO0_4), RN3.5 (R4.2)
PB5: IC1.9 (IO0_5), RN3.6 (R3.2)
PB6: IC1.10 (IO0_6), RN3.7 (R2.2)
PB7: IC1.12 (IO0_7), RN3.8 (R1.2)
PB8: IC1.13 (IO1_0), RN2.5 (R4.2)
PB9: IC1.14 (IO1_1), RN2.6 (R3.2)
PB10: IC1.15 (IO1_2), RN2.7 (R2.2)
PB11: IC1.16 (IO1_3), RN2.8 (R1.2)
RESET: IC1.56 (~RESET), J2.4

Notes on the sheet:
gpio 7
gpio 10
gpio 5
gpio 8
gpio 3
HEADER

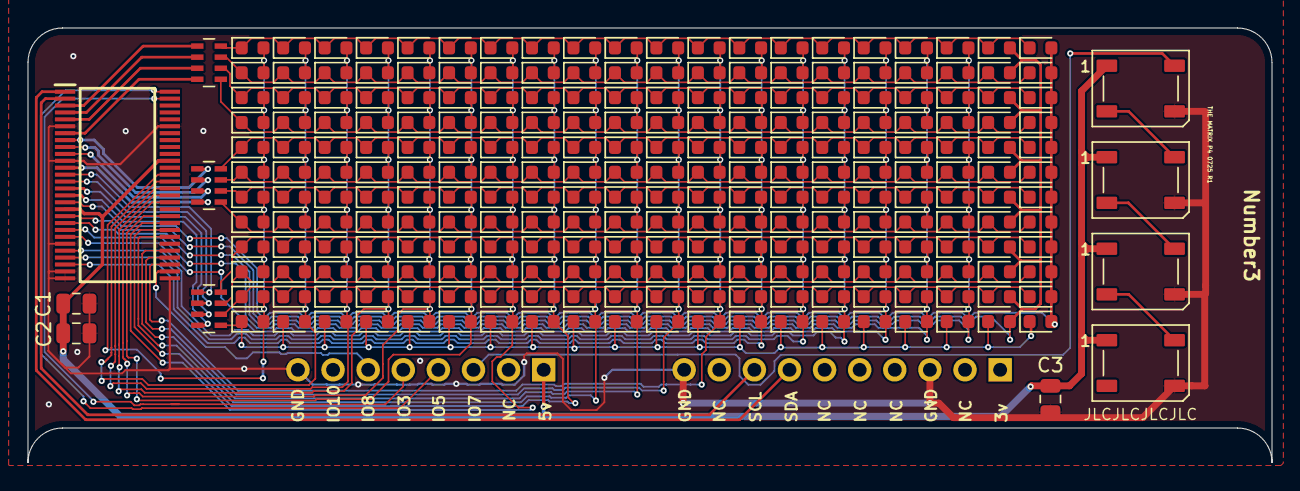
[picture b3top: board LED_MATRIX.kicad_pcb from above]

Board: 2 copper layers, 90.0 x 31.4 mm, 253 parts (0 on the bottom side), 55 nets.

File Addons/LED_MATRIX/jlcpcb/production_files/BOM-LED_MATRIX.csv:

Comment,Designator,Footprint,LCSC,Quantity
1k,"RN1,RN2,RN3",R_Array_Concave_4x0603,C111803,3
100nF,"C2,C3",C_0805_2012Metric,C1711,2
10uF,C1,C_0805_2012Metric,C1713,1
LED0603,"D1,D10,D100,D101,D102,D103,D104,D105,D106,D107,D108,D109,D11,D110,D111,D112,D113,D114,D115,D116,D117,D118,D119,D12,D120,D121,D122,D123,D124,D125,D126,D127,D128,D129,D13,D130,D131,D132,D133,D134,D135,D136,D137,D138,D139,D14,D140,D141,D142,D143,D144,D145,D146,D147,D148,D149,D15,D150,D151,D152,D153,D154,D155,D156,D157,D158,D159,D16,D160,D161,D162,D163,D164,D165,D166,D167,D168,D169,D17,D170,D171,D172,D173,D174,D175,D176,D177,D178,D179,D18,D180,D181,D182,D183,D184,D185,D186,D187,D188,D189,D19,D190,D191,D192,D193,D194,D195,D196,D197,D198,D199,D2,D20,D200,D201,D202,D203,D204,D205,D206,D207,D208,D209,D21,D210,D211,D212,D213,D214,D215,D216,D217,D218,D219,D22,D220,D221,D222,D223,D224,D225,D226,D227,D228,D229,D23,D230,D231,D232,D233,D234,D235,D236,D237,D238,D239,D24,D240,D25,D26,D27,D28,D29,D3,D30,D31,D32,D33,D34,D35,D36,D37,D38,D39,D4,D40,D41,D42,D43,D44,D45,D46,D47,D48,D49,D5,D50,D51,D52,D53,D54,D55,D56,D57,D58,D59,D6,D60,D61,D62,D63,D64,D65,D66,D67,D68,D69,D7,D70,D71,D72,D73,D74,D75,D76,D77,D78,D79,D8,D80,D81,D82,D83,D84,D85,D86,D87,D88,D89,D9,D90,D91,D92,D93,D94,D95,D96,D97,D98,D99",LED_0603_1608Metric,C19273151,240
WS2812B,"D241,D242,D243,D244",LED_WS2812B_PLCC4_5.0x5.0mm_P3.2mm,C22464516,4
Conn_01x08_Pin,J2,PinHeader_1x08_P2.54mm_Horizontal,C492416,1
Conn_01x10_Pin,J1,PinHeader_1x10_P2.54mm_Horizontal,C492418,1
PCA9698DGG,IC1,SOP50P810X120-56N,C729177,1

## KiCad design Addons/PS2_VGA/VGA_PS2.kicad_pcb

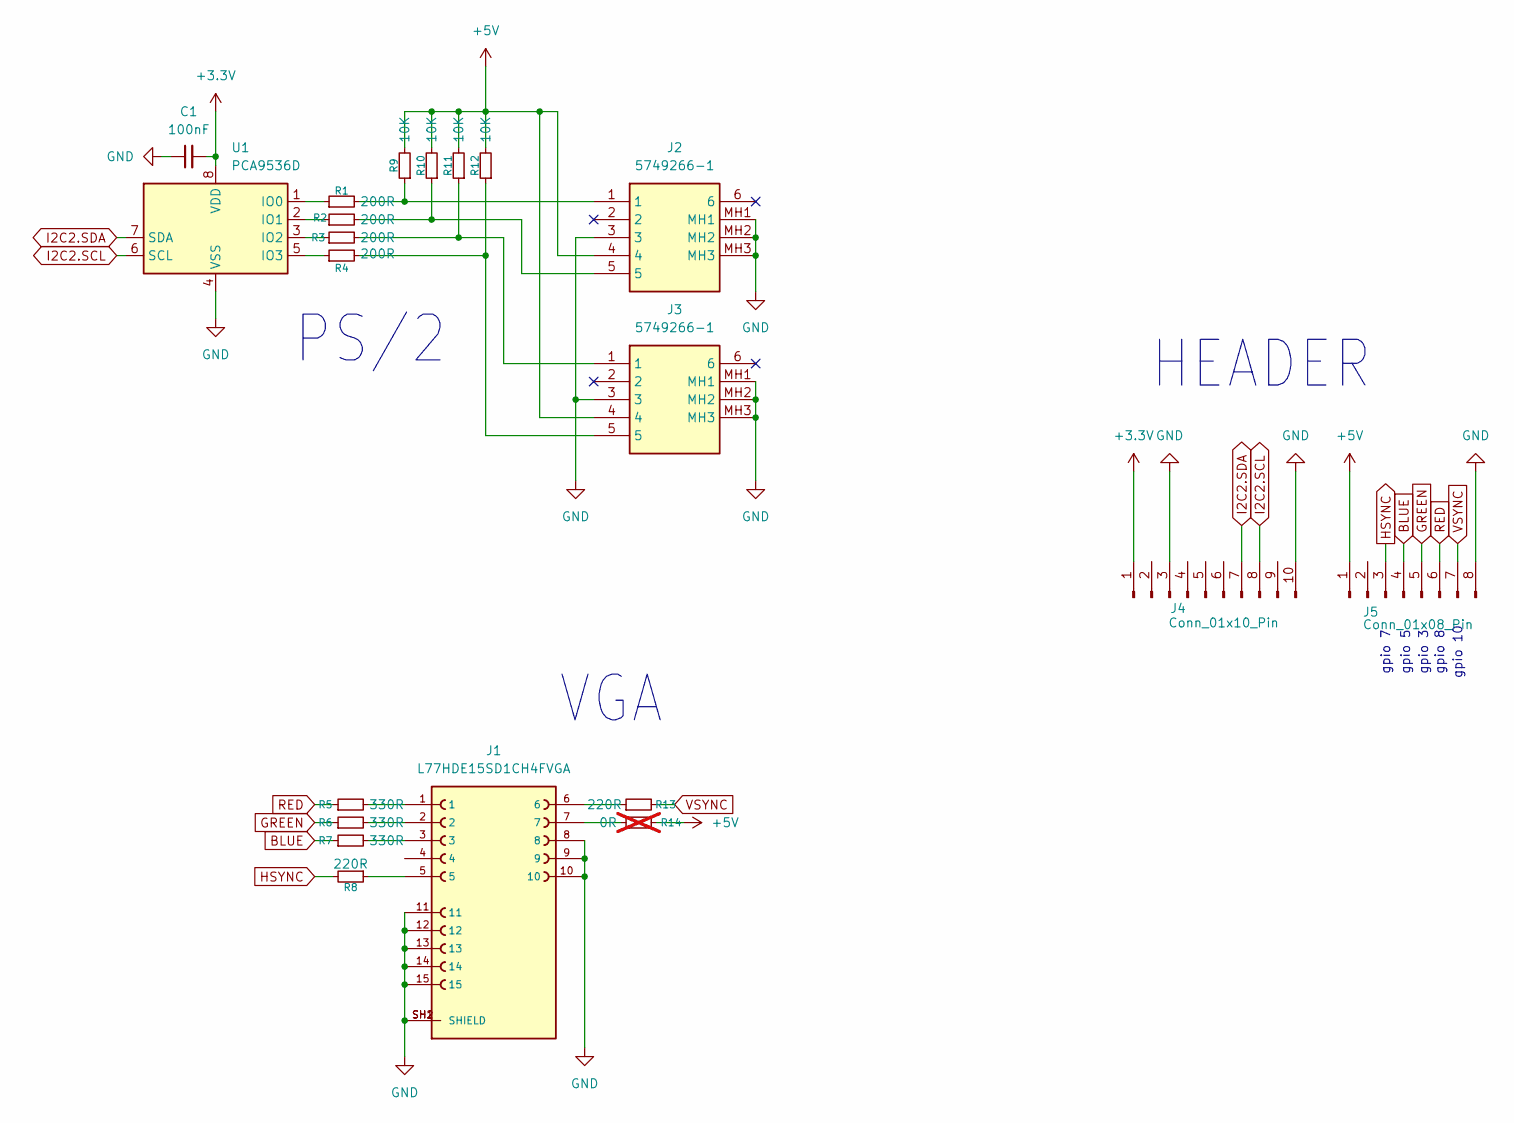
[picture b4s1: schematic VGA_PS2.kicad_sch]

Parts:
C1: 100nF; C_0805_2012Metric
J1: L77HDE15SD1CH4FVGA; AMPHENOL_L77HDE15SD1CH4FVGA; PARTREV 1
J2, J3: 5749266-1; 57492661; Manufacturer_Part_Number 5749266-1; Mouser Part Number 571-5749266-1
J4: Conn_01x10_Pin; PinHeader_1x10_P2.54mm_Horizontal
J5: Conn_01x08_Pin; PinHeader_1x08_P2.54mm_Horizontal
R1, R2, R3, R4: 200R; R_0805_2012Metric; LCSC C17168
R5, R6, R7: 330R; R_0805_2012Metric; LCSC C17168
R8, R13: 220R; R_0805_2012Metric; LCSC C17168
R9, R10, R11, R12: 10K; R_0805_2012Metric; LCSC C17168
R14: 0R; R_0805_2012Metric; LCSC C17168; not fitted
U1: PCA9536D; SOIC-8_3.9x4.9mm_P1.27mm

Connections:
+3.3V: C1.2, J4.1, U1.8 (VDD)
+5V: J2.4, J3.4, J5.1, R9.2, R10.2, R11.2, R12.2, R14.2
BLUE: J5.4, R7.1
GND: C1.1, J1.8, J1.9, J1.10, J1.11, J1.12, J1.13, J1.14, J1.15, J1.SH1 (SHIELD), J1.SH2 (SHIELD), J2.3, J2.MH1, J2.MH2, J2.MH3, J3.3, J3.MH1, J3.MH2, J3.MH3, J4.3, J4.10, J5.8, U1.4 (VSS)
GREEN: J5.5, R6.1
HSYNC: J5.3, R8.2
I2C2.SCL: J4.8, U1.6 (SCL)
I2C2.SDA: J4.7, U1.7 (SDA)
unnamed: J1.1, R5.2
unnamed: J1.2, R6.2
unnamed: J1.3, R7.2
unnamed: J1.5, R8.1
unnamed: J1.6, R13.1
unnamed: J1.7, R14.1
unnamed: J2.1, R1.2, R9.1
unnamed: J2.5, R2.2, R10.1
unnamed: J3.1, R3.2, R11.1
unnamed: J3.5, R4.2, R12.1
unnamed: R1.1, U1.1 (IO0)
unnamed: R2.1, U1.2 (IO1)
unnamed: R3.1, U1.3 (IO2)
unnamed: R4.1, U1.5 (IO3)
RED: J5.6, R5.1
VSYNC: J5.7, R13.2

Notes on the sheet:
gpio 7
gpio 10
PS/2
VGA
gpio 5
gpio 8
gpio 3
HEADER
